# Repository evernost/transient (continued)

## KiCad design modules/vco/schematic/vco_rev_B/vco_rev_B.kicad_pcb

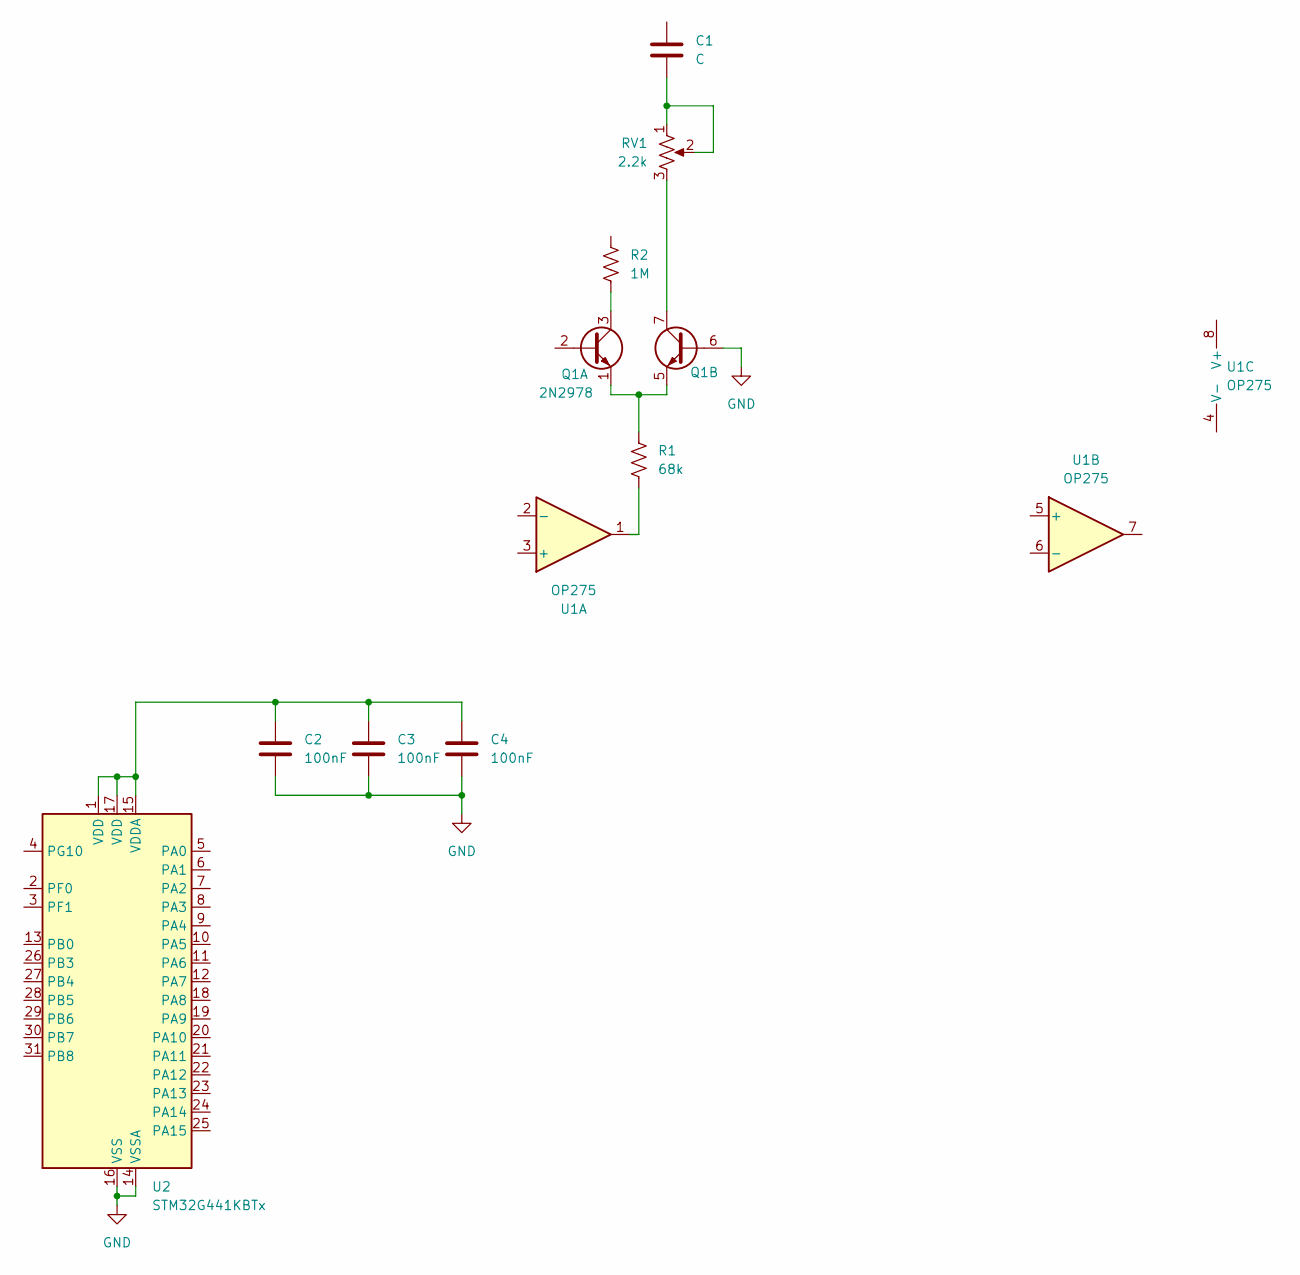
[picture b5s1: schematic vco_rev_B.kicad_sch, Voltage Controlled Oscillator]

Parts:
C1: C; C_Rect_L7.0mm_W2.0mm_P5.00mm
C2, C3, C4: 100nF; C_0805_2012Metric_Pad1.18x1.45mm_HandSolder
Q1: 2N2978; TO-5-6
R1: 68k; R_Axial_DIN0207_L6.3mm_D2.5mm_P10.16mm_Horizontal
R2: 1M; R_Axial_DIN0207_L6.3mm_D2.5mm_P10.16mm_Horizontal
RV1: 2.2k; Potentiometer_Bourns_3296W_Vertical
U1: OP275; DIP-8_W7.62mm_Socket_LongPads
U2: STM32G441KBTx; LQFP-32_7x7mm_P0.8mm

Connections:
GND: C2.2, C3.2, C4.2, Q1.6 (B2), U2.14 (VSSA), U2.16 (VSS), U2.32 (VSS)
unnamed: C1.2, RV1.1, RV1.2
unnamed: Q1.3 (C1), R2.2
unnamed: Q1.1 (E1), Q1.5 (E2), R1.1
unnamed: Q1.7 (C2), RV1.3
unnamed: R1.2, U1.1
unnamed: C2.1, C3.1, C4.1, U2.1 (VDD), U2.15 (VDDA), U2.17 (VDD)

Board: 2 copper layers, 10 parts (0 on the bottom side), 7 nets, no tracks yet.

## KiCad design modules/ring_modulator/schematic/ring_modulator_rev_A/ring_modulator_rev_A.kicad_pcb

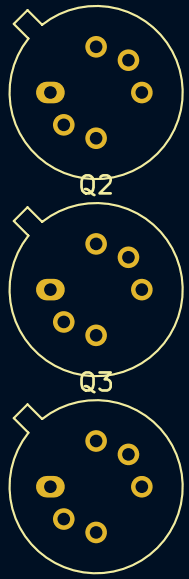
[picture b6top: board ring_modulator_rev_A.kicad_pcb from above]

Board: 2 copper layers, 3 parts (0 on the bottom side), 5 nets, no tracks yet.

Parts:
Q1, Q2, Q3: 2N2978; TO-5-6

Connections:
unnamed: Q1.2 (B1), Q2.6 (B2)
unnamed: Q1.1 (E1), Q1.5 (E2), Q3.3 (C1)
unnamed: Q1.6 (B2), Q2.2 (B1)
unnamed: Q2.1 (E1), Q2.5 (E2), Q3.7 (C2)
unnamed: Q3.1 (E1), Q3.5 (E2)

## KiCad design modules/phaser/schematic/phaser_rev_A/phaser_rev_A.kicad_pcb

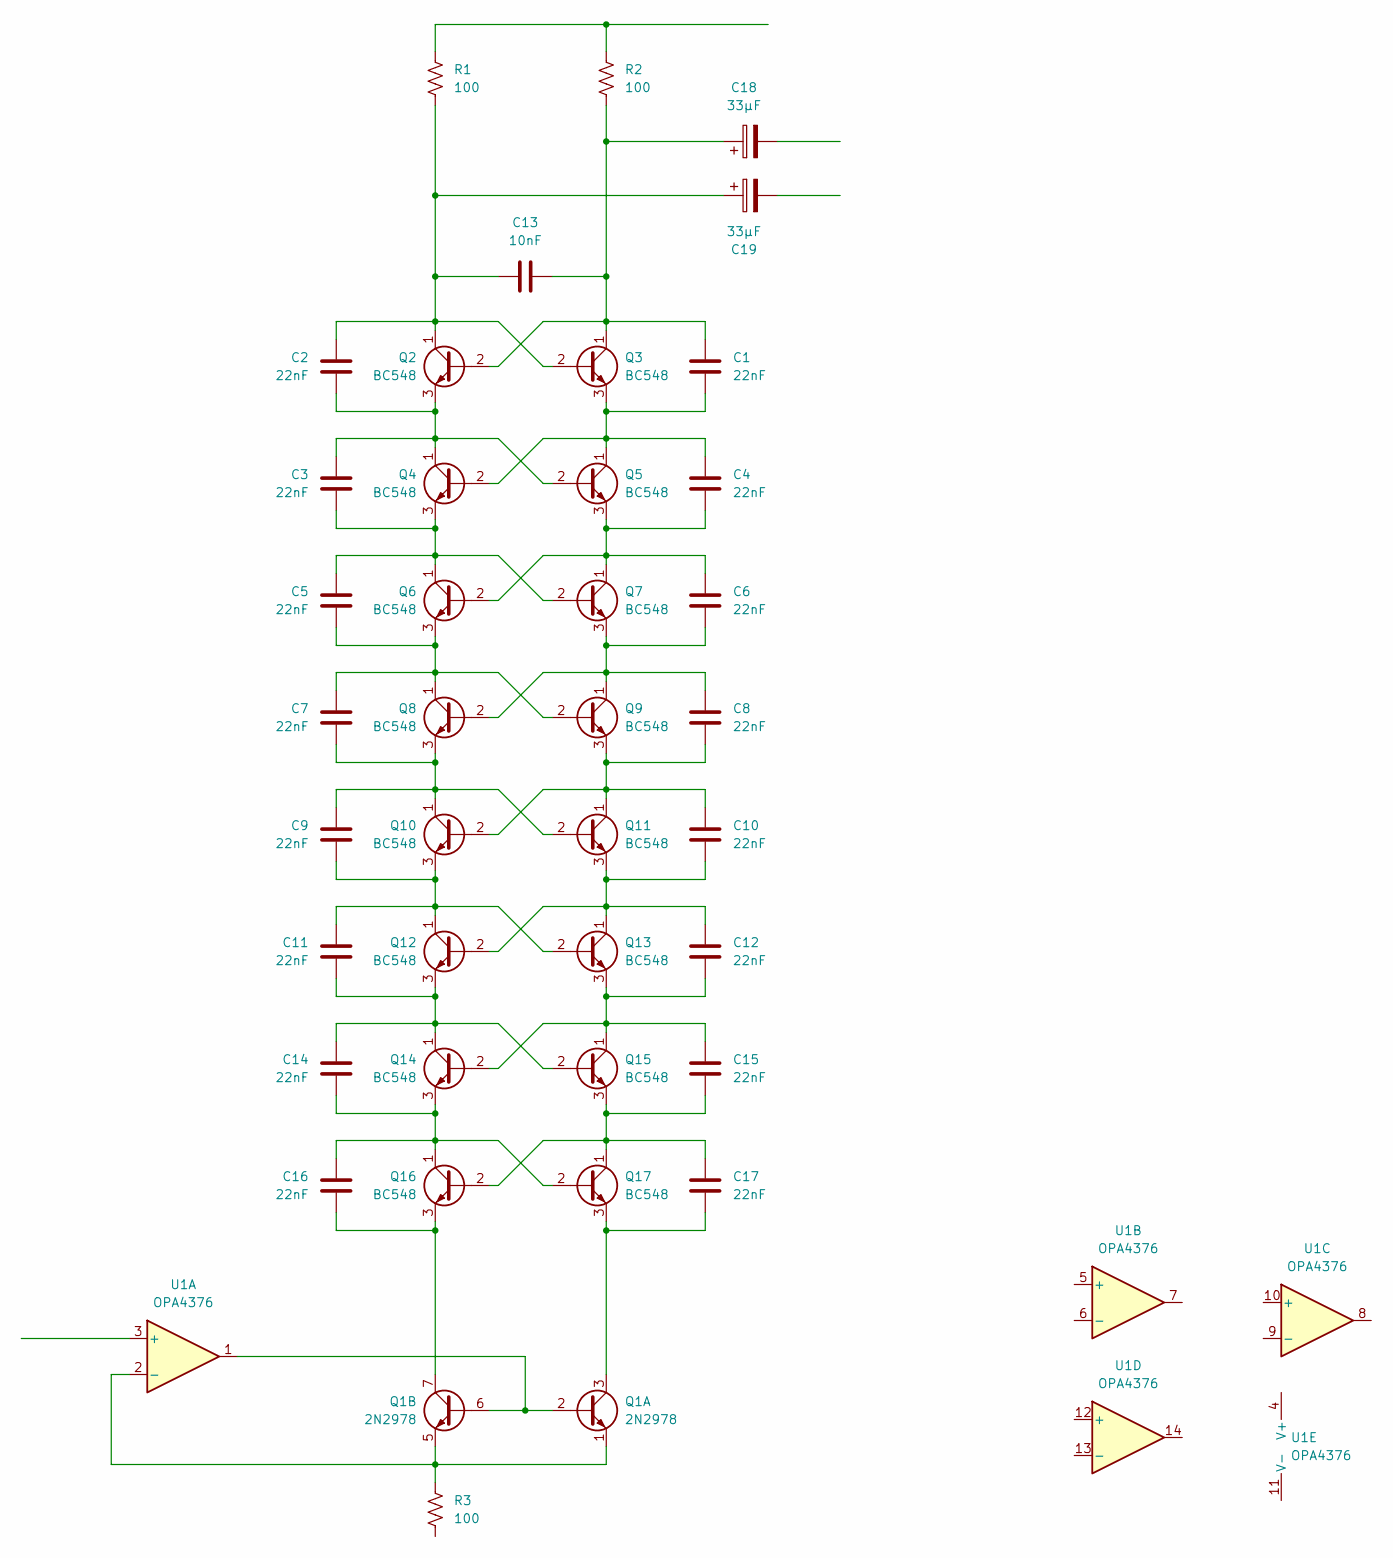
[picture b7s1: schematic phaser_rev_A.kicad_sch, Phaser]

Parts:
C1, C2, C3, C4, C5, C6, C7, C8, C9, C10, C11, C12, C14, C15, C16, C17: 22nF; C_Rect_L7.0mm_W2.0mm_P5.00mm
C13: 10nF; C_Rect_L7.0mm_W2.0mm_P5.00mm
C18, C19: 33µF; CP_Radial_D8.0mm_P3.80mm
Q1: 2N2978; TO-5-6
Q2, Q3, Q4, Q5, Q6, Q7, Q8, Q9, Q10, Q11, Q12, Q13, Q14, Q15, Q16, Q17: BC548; TO-92L_Inline_Wide
R1, R2, R3: 100; R_Axial_DIN0207_L6.3mm_D2.5mm_P10.16mm_Horizontal
U1: OPA4376; DIP-14_W7.62mm_LongPads

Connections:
unnamed: Q1.2 (B1), Q1.6 (B2), U1.1
unnamed: Q1.1 (E1), Q1.5 (E2), R3.1, U1.2 (-)
unnamed: C1.1, C13.2, C18.1, Q2.2 (B), Q3.1 (C), R2.2
unnamed: C2.1, C13.1, C19.1, Q2.1 (C), Q3.2 (B), R1.2
unnamed: C2.2, C3.1, Q2.3 (E), Q4.1 (C), Q5.2 (B)
unnamed: C1.2, C4.1, Q3.3 (E), Q4.2 (B), Q5.1 (C)
unnamed: C3.2, C5.1, Q4.3 (E), Q6.1 (C), Q7.2 (B)
unnamed: C4.2, C6.1, Q5.3 (E), Q6.2 (B), Q7.1 (C)
unnamed: C5.2, C7.1, Q6.3 (E), Q8.1 (C), Q9.2 (B)
unnamed: C6.2, C8.1, Q7.3 (E), Q8.2 (B), Q9.1 (C)
unnamed: C8.2, C10.1, Q9.3 (E), Q10.2 (B), Q11.1 (C)
unnamed: C7.2, C9.1, Q8.3 (E), Q10.1 (C), Q11.2 (B)
unnamed: C9.2, C11.1, Q10.3 (E), Q12.1 (C), Q13.2 (B)
unnamed: C10.2, C12.1, Q11.3 (E), Q12.2 (B), Q13.1 (C)
unnamed: C11.2, C14.1, Q12.3 (E), Q14.1 (C), Q15.2 (B)
unnamed: C12.2, C15.1, Q13.3 (E), Q14.2 (B), Q15.1 (C)
unnamed: C14.2, C16.1, Q14.3 (E), Q16.1 (C), Q17.2 (B)
unnamed: C15.2, C17.1, Q15.3 (E), Q16.2 (B), Q17.1 (C)
unnamed: C16.2, Q1.7 (C2), Q16.3 (E)
unnamed: C17.2, Q1.3 (C1), Q17.3 (E)

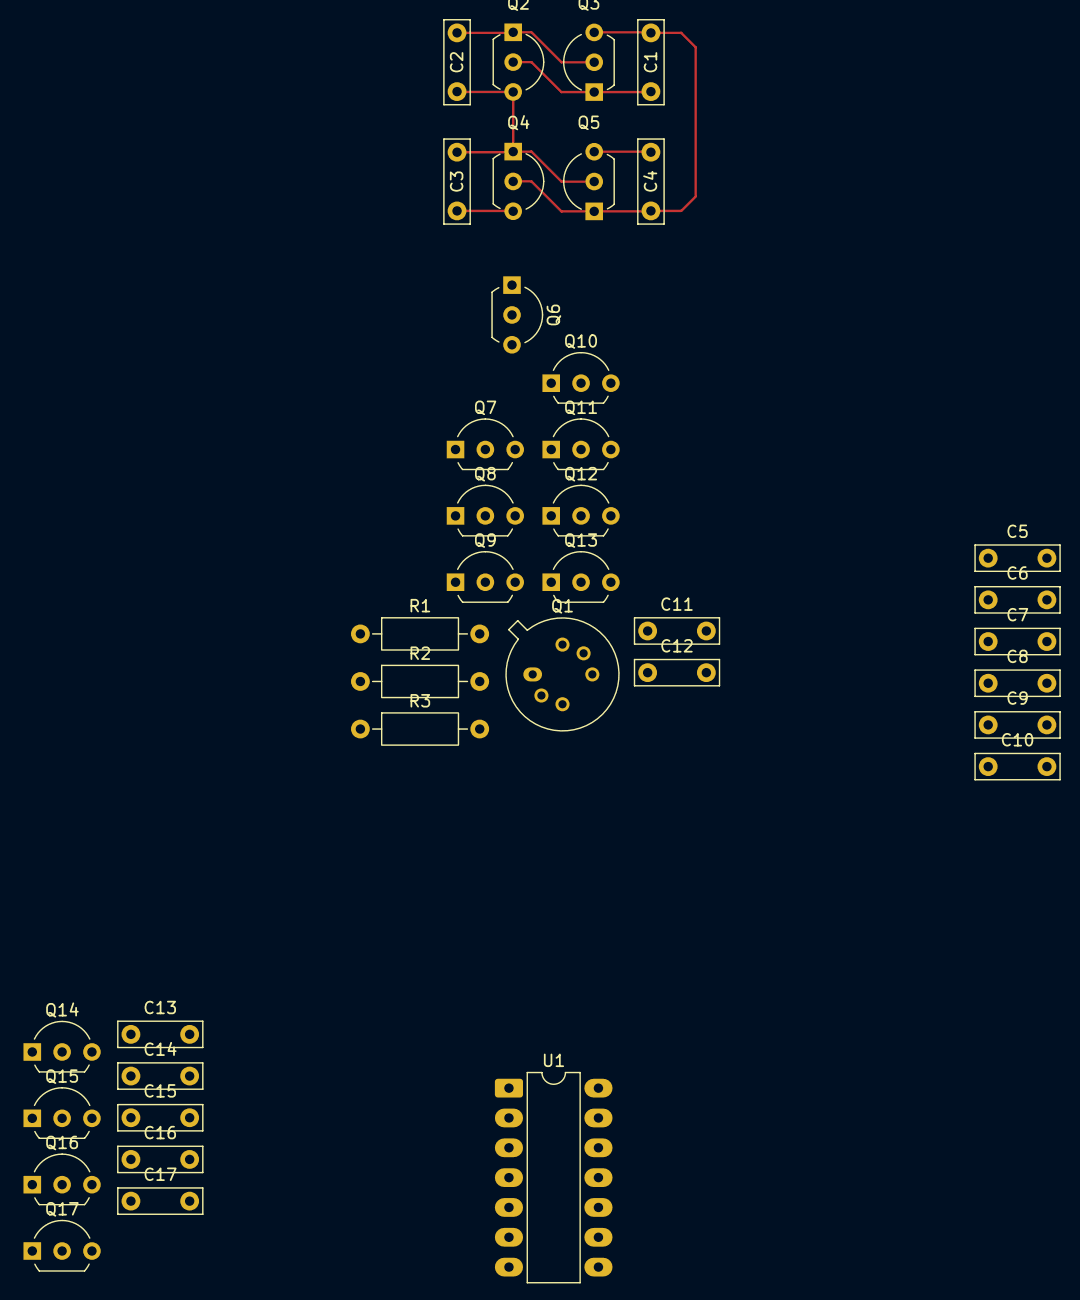
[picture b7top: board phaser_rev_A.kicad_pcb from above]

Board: 2 copper layers, 38 parts (0 on the bottom side), 20 nets.

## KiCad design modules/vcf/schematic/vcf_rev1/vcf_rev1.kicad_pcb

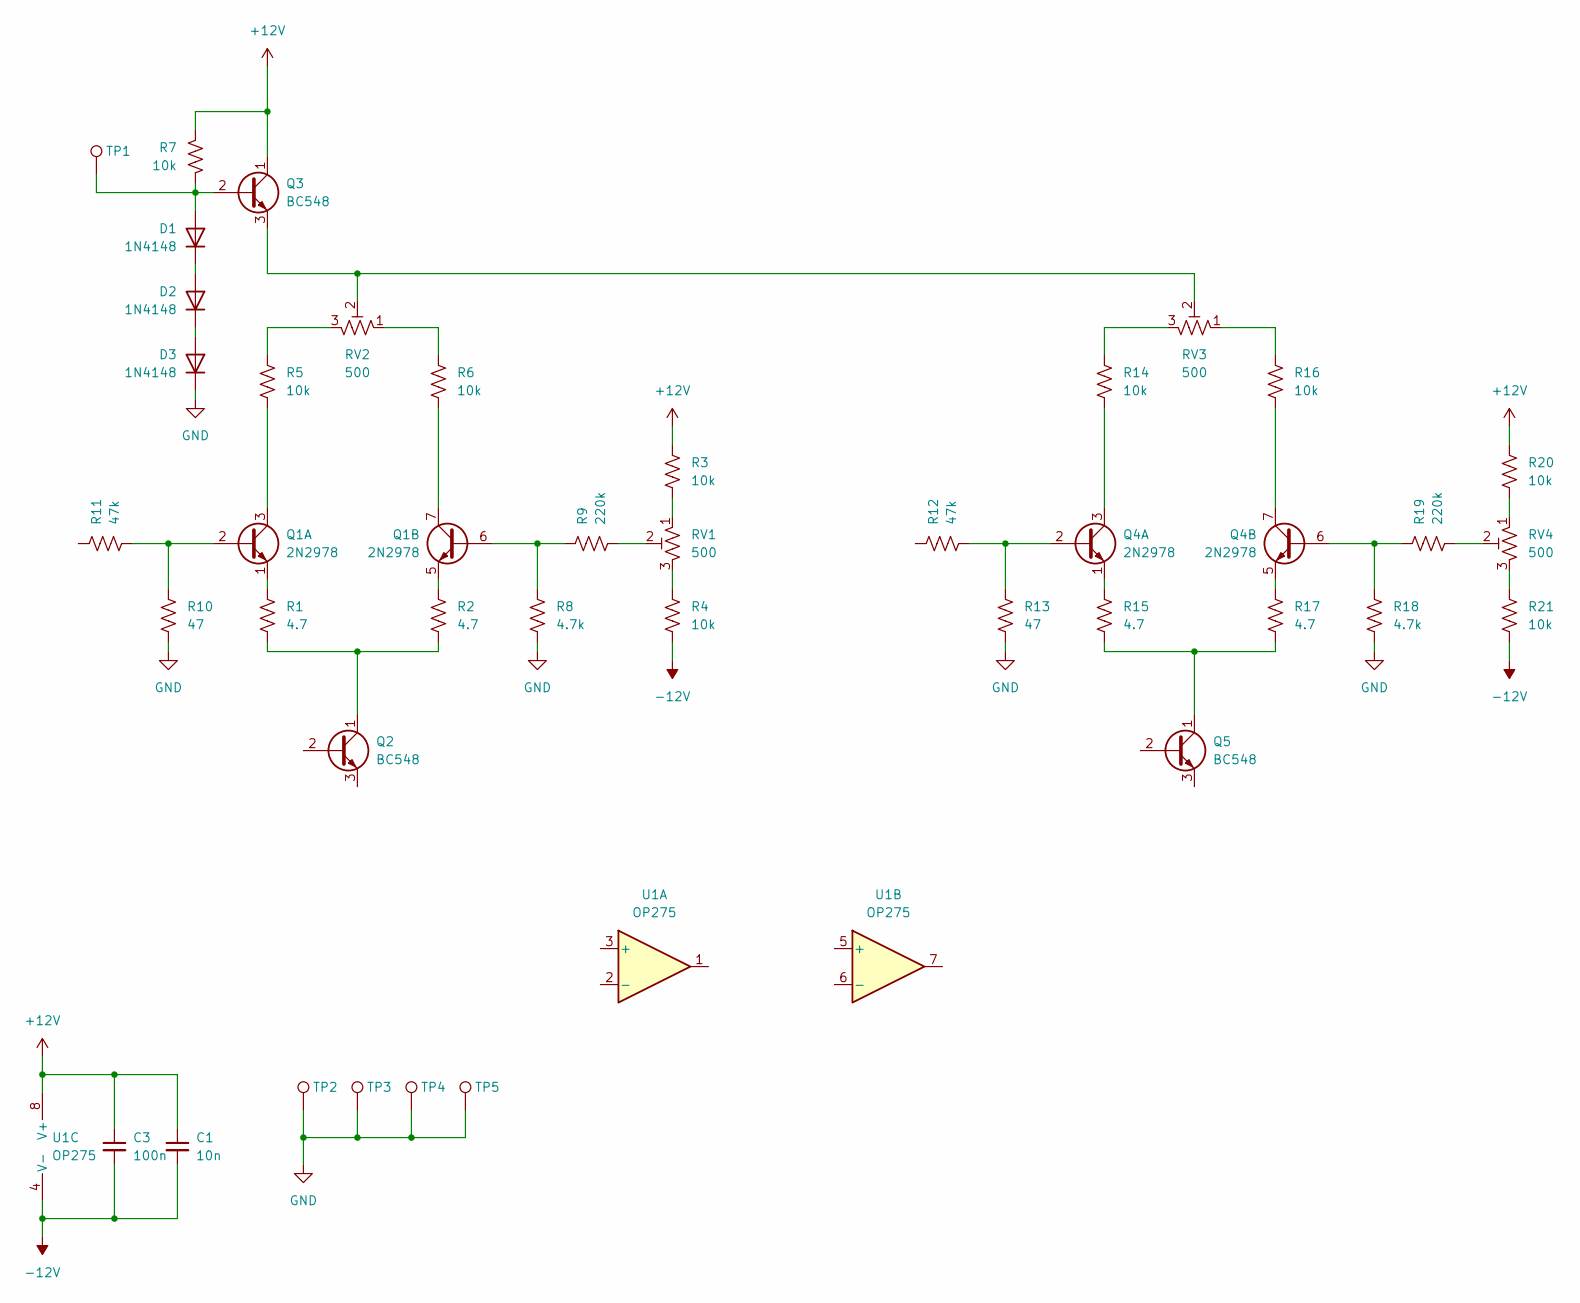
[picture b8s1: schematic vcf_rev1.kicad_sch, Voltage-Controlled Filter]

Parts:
C1: 10n; C_Rect_L7.0mm_W2.0mm_P5.00mm
C3: 100n; C_Rect_L7.0mm_W2.0mm_P5.00mm
D1, D2, D3: 1N4148; D_DO-35_SOD27_P7.62mm_Horizontal
Q1, Q4: 2N2978; TO-5-6
Q2, Q3, Q5: BC548; TO-92_Inline
R1, R2, R15, R17: 4.7; R_Axial_DIN0207_L6.3mm_D2.5mm_P10.16mm_Horizontal
R3, R4, R5, R6, R7, R14, R16, R20, R21: 10k; R_Axial_DIN0207_L6.3mm_D2.5mm_P10.16mm_Horizontal
R8, R18: 4.7k; R_Axial_DIN0207_L6.3mm_D2.5mm_P10.16mm_Horizontal
R9, R19: 220k; R_Axial_DIN0207_L6.3mm_D2.5mm_P10.16mm_Horizontal
R10, R13: 47; R_Axial_DIN0207_L6.3mm_D2.5mm_P10.16mm_Horizontal
R11, R12: 47k; R_Axial_DIN0207_L6.3mm_D2.5mm_P10.16mm_Horizontal
RV1, RV2, RV3, RV4: 500; Potentiometer_Bourns_3296W_Vertical
TP1, TP2, TP3, TP4, TP5: TestPoint; TestPoint_Pad_D2.0mm
U1: OP275; DIP-8_W7.62mm_Socket_LongPads

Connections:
+12V: C1.1, C3.1, Q3.1 (C), R3.1, R7.1, R20.1, U1.8 (V+)
-12V: C1.2, C3.2, R4.2, R21.2, U1.4 (V-)
GND: D3.1 (K), R8.2, R10.2, R13.2, R18.2, TP2.1, TP3.1, TP4.1, TP5.1
unnamed: D1.2 (A), Q3.2 (B), R7.2, TP1.1
unnamed: D1.1 (K), D2.2 (A)
unnamed: D2.1 (K), D3.2 (A)
unnamed: Q1.2 (B1), R10.1, R11.2
unnamed: Q1.3 (C1), R5.2
unnamed: Q1.1 (E1), R1.1
unnamed: Q1.6 (B2), R8.1, R9.1
unnamed: Q1.7 (C2), R6.2
unnamed: Q1.5 (E2), R2.1
unnamed: Q2.1 (C), R1.2, R2.2
unnamed: Q3.3 (E), RV2.2, RV3.2
unnamed: Q4.2 (B1), R12.2, R13.1
unnamed: Q4.3 (C1), R14.2
unnamed: Q4.1 (E1), R15.1
unnamed: Q4.6 (B2), R18.1, R19.1
unnamed: Q4.7 (C2), R16.2
unnamed: Q4.5 (E2), R17.1
unnamed: Q5.1 (C), R15.2, R17.2
unnamed: R3.2, RV1.1
unnamed: R4.1, RV1.3
unnamed: R5.1, RV2.3
unnamed: R6.1, RV2.1
unnamed: R9.2, RV1.2
unnamed: R14.1, RV3.3
unnamed: R16.1, RV3.1
unnamed: R19.2, RV4.2
unnamed: R20.2, RV4.1
unnamed: R21.1, RV4.3

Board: 2 copper layers, 41 parts (0 on the bottom side), 31 nets, no tracks yet.

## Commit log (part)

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2025-10-30 added db for the headphones amplifier
2025-10-31 added the VCA module
2025-11-03 added an overload detector to the headphone amp
2026-01-01 added the VCF submodules added the voltage controlled current sink
2026-01-04 Added project library Added 2N2978
2026-01-13 added the article were justifications will be detailed added framework where the distorsion will be evaluated
2026-01-14 fixed the VCA for the filter in simulation, added sections in the doc for the VCF
2026-01-15 added some more tools, standardised code format
2026-01-18 added schematic for the headphones amplifier
2026-01-19 added reference schematic added dev directories
2026-01-20 updated the schematic for the ring mod to a working example
2026-01-21 added schematic (principle) for the 'rabotnik' module
2026-01-24 added the noise generator module
2026-01-25 updated schematic for the headphones amp and VCF
2026-01-25 renamed the noise module to something more accurate'
2026-01-27 added readme for the VCO
2026-01-27 added the VCA kicad project
2026-01-28 updated descriptions
2026-01-29 added schematic for the noise generator
2026-01-30 added .gitignore definitions added schematics for the ring modulator and vco
2026-01-30 renamed the headphones amplifier project added a list of commonly used parts
2026-01-31 added some docs
2026-02-01 renamed the VCF project files
2026-02-01 added the PPL
2026-02-02 added reference schematics
2026-02-02 added new references to the PPL
2026-02-03 updated the calculations/simulations/schematic for the headphones amp
2026-02-03 restructured the libraries folders
2026-02-04 fixed the path to libraries (relative instead of absolute)
2026-02-05 added first footprint attempt completed the .gitignore list
2026-02-06 added a description for the project library completed the footprint for PTV potentiometer
2026-02-07 added proper silkscreen on PTV potentiometer
2026-02-07 replaced footprint for the PTV potentiometer with an existing version (with minor tweaks)
2026-02-07 updated the Bourns PTV112 updated schematic renamed and upgraded the list of commonly used kicad parts
2026-02-08 added the datasheet of the parts in the PPL
2026-02-08 added footprint for the ANT switch
2026-02-09 updated ignore list updated library with a new switch (ANT)
2026-02-10 added draft footprint for the Wurth Connector
2026-02-11 attempt to fix wrong footprint
2026-02-12 fixed the footprint issue with the PTV
2026-02-13 added datasheets
2026-02-14 added footprint for the 5.08mm board connector
2026-02-15 added outline for the PCB
2026-02-16 updated the pcb outline
2026-02-18 extended PCB outline
2026-02-19 adjusted bias point of the input stage first preplacement of the parts on the board
2026-02-20 fixed the lib path in the VCO project
2026-02-24 updated the article
2026-02-25 updated rubber diode section
2026-03-03 - added a bootstrap structure for improved input impedance - moved the mono/stereo junction point
2026-03-07 input stage: improved biasing (more stable version), added component values (validated on prototype) PCB cleanup (useless footprints)
2026-03-09 added project for the Phasing module
2026-03-10 first routing of the PCB added a case study for the phaser
2026-03-11 added an article about the phaser derivation + illustrating simulation
2026-03-12 updated pcb layout
2026-03-16 added on board measurements
2026-03-18 progress backup
2026-03-19 PCB progress backup
2026-03-22 PCB progress backup All parts finally fit in the board!
2026-03-23 added a PDF export of the schematic
2026-03-24 added STM32 preliminary project for the VCO
2026-06-06 progressed on the routing
